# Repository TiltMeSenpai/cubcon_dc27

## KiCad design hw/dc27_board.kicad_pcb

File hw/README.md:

# Defcon 27 Cubcon Badge
Electronic badge from Defcon 27 (2019).  
Contact [@tiltmesenpai](https://twitter.com/TiltMeSenpai) or [@_cubcon](https://twitter.com/_cubcon) on Twitter with any questions.

## Important Eratta
- R1, C17 (On boards given out at Defcon) should be left unpopulated.
  These have been removed in this release.
- Button support components map according to the following table:

| Defcon Board | Post-Defcon Board |
|---|---|
| R2 | R1 |
| R3 | R4 |
| R3 | R2 |
| C16 | C4 |
| C14 | C6 |
| C15 | C5 |

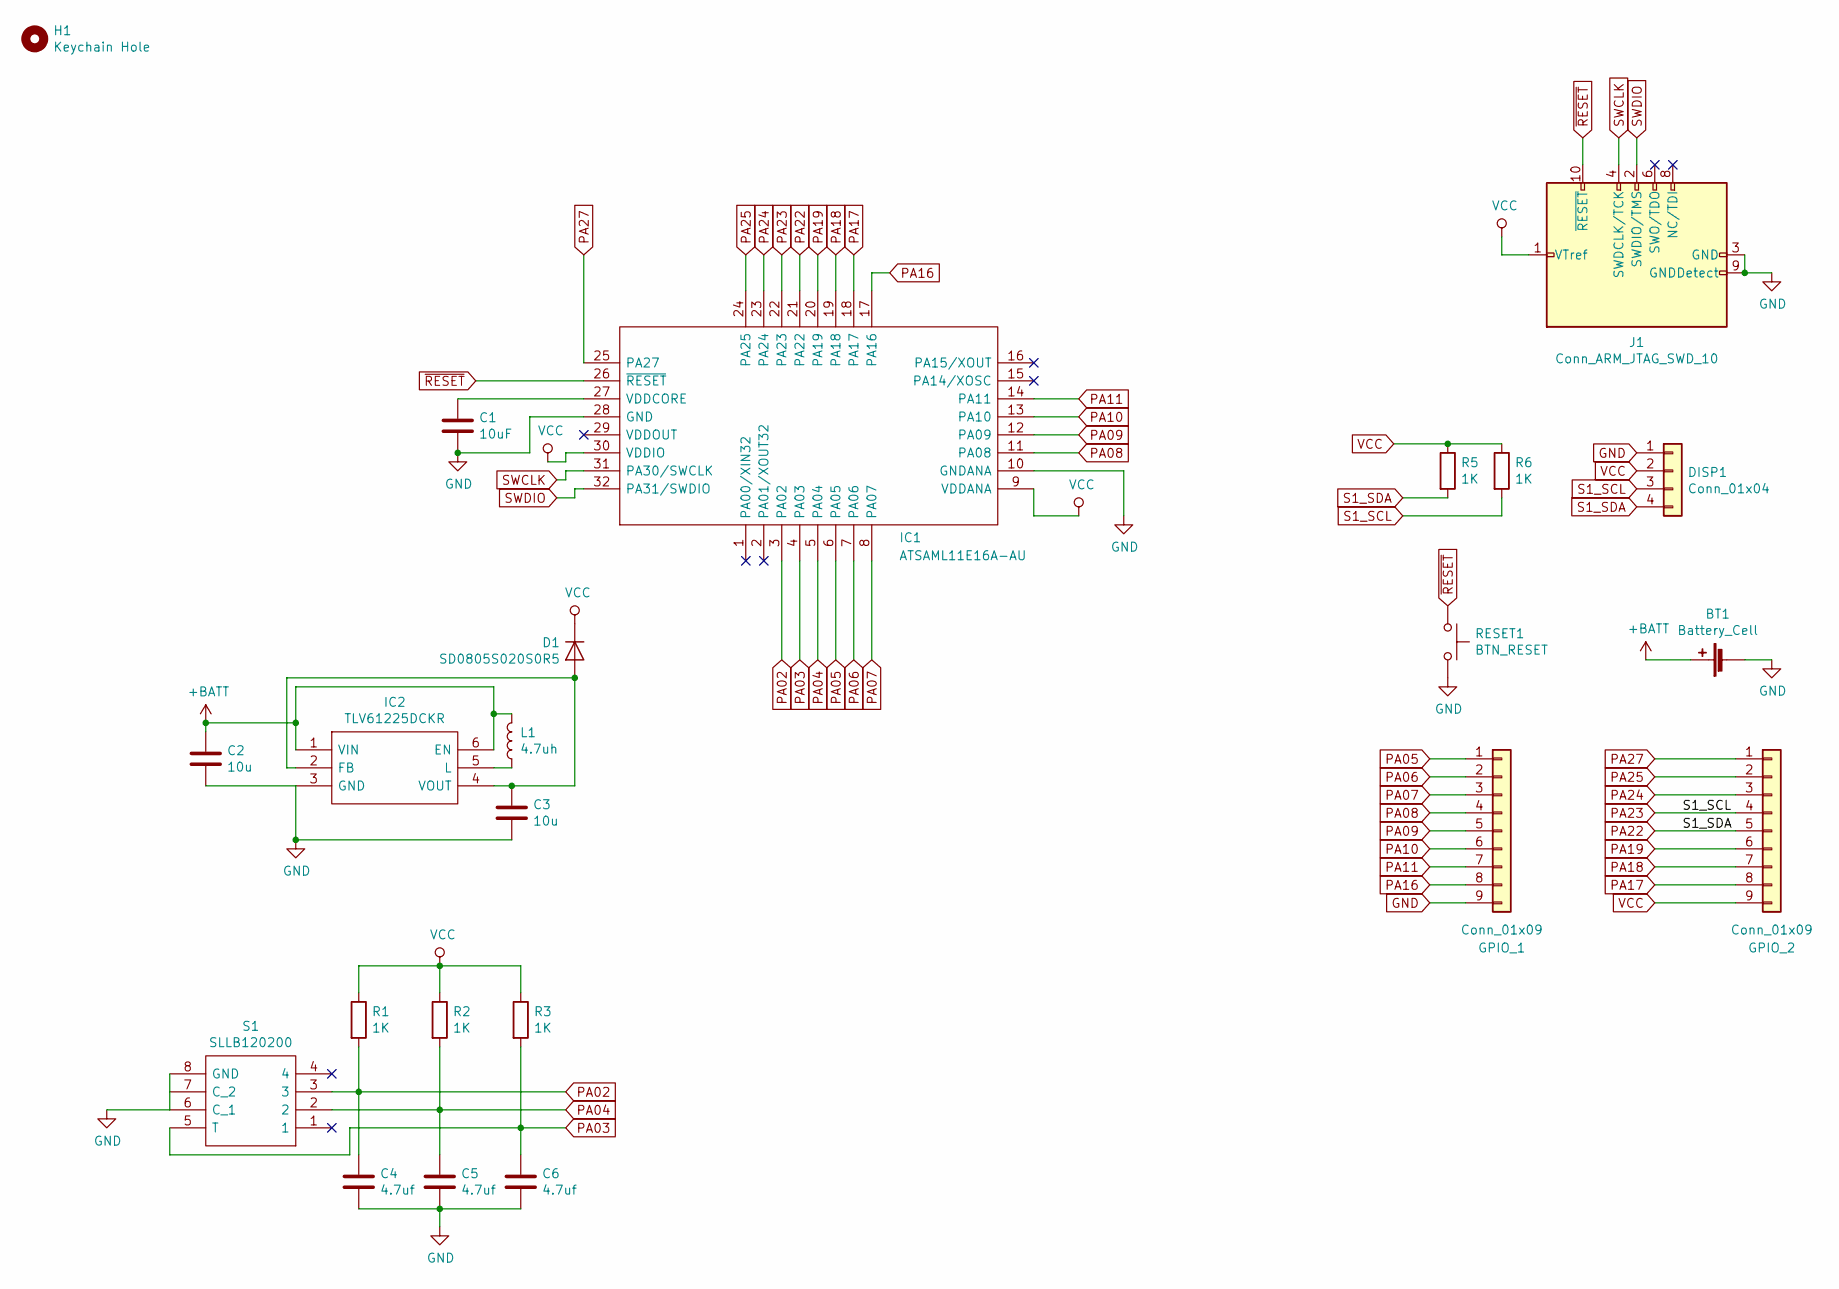
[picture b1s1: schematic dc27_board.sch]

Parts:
BT1: Battery_Cell; 2466; Mouser Part Number 534-2466
C1: 10uF; C_0805_2012Metric_Pad1.15x1.40mm_HandSolder
C2, C3: 10u; C_0805_2012Metric_Pad1.15x1.40mm_HandSolder; Mouser Part Number 80-C0805X106M9RAUTO
C4, C5, C6: 4.7uf; C_0805_2012Metric_Pad1.15x1.40mm_HandSolder
D1: SD0805S020S0R5; D_0805_2012Metric; Mouser Part Number 581-SD0805S020S0R5
DISP1: Conn_01x04; PinHeader_1x04_P2.54mm_Vertical
GPIO_1, GPIO_2: Conn_01x09; PinSocket_1x09_P2.54mm_Vertical
H1: Keychain Hole; MountingHole_2mm
IC1: ATSAML11E16A-AU; QFP80P900X900X120-32N; Mouser Part Number 579-ATSAML11E16A-AU
IC2: TLV61225DCKR; SOT65P210X110-6N; Mouser Part Number 595-TLV61225DCKR
J1: Conn_ARM_JTAG_SWD_10; PinHeader_2x05_P1.27mm_Vertical_SMD; Mouser Part Number 855-M50-3610542
L1: 4.7uh; L_0805_2012Metric_Pad1.15x1.40mm_HandSolder; Mouser Part Number 652-SRN2009T-4R7M
R1, R2, R3: 1K; C_0805_2012Metric_Pad1.15x1.40mm_HandSolder
R5, R6: 1K; R_0805_2012Metric_Pad1.15x1.40mm_HandSolder; Mouser Part Number 667-ERJ-UP6J102V
RESET1: BTN_RESET; SW_SPST_TL3342
S1: SLLB120200; Mouser Part Number 688-SLLB120200

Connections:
+BATT: BT1.1 (+), C2.1, IC2.1 (VIN), IC2.6 (EN), L1.2
GND: BT1.2 (-), C1.2, C2.2, C3.2, C4.2, C5.2, C6.2, DISP1.1, GPIO_1.9, IC1.10 (GNDANA), IC1.28 (GND), IC2.3 (GND), J1.3 (GND), J1.5 (GND), J1.9 (GNDDetect), RESET1.2, S1.6 (C_1), S1.8 (GND)
unnamed: C1.1, IC1.27 (VDDCORE)
unnamed: C3.1, D1.2 (A), IC2.2 (FB), IC2.4 (VOUT)
unnamed: IC2.5 (L), L1.1
PA02: C4.1, IC1.3 (PA02), R1.2, S1.3
PA03: C6.1, IC1.4 (PA03), R3.2, S1.5 (T)
PA04: C5.1, IC1.5 (PA04), R2.2, S1.2
PA05: GPIO_1.1, IC1.6 (PA05)
PA06: GPIO_1.2, IC1.7 (PA06)
PA07: GPIO_1.3, IC1.8 (PA07)
PA08: GPIO_1.4, IC1.11 (PA08)
PA09: GPIO_1.5, IC1.12 (PA09)
PA10: GPIO_1.6, IC1.13 (PA10)
PA11: GPIO_1.7, IC1.14 (PA11)
PA16: GPIO_1.8, IC1.17 (PA16)
PA17: GPIO_2.8, IC1.18 (PA17)
PA18: GPIO_2.7, IC1.19 (PA18)
PA19: GPIO_2.6, IC1.20 (PA19)
PA22: DISP1.4, GPIO_2.5, IC1.21 (PA22), R5.2
PA23: DISP1.3, GPIO_2.4, IC1.22 (PA23), R6.2
PA24: GPIO_2.3, IC1.23 (PA24)
PA25: GPIO_2.2, IC1.24 (PA25)
PA27: GPIO_2.1, IC1.25 (PA27)
SWCLK: IC1.31 (PA30/SWCLK), J1.4 (SWDCLK/TCK)
SWDIO: IC1.32 (PA31/SWDIO), J1.2 (SWDIO/TMS)
VCC: D1.1 (K), DISP1.2, GPIO_2.9, IC1.9 (VDDANA), IC1.30 (VDDIO), J1.1 (VTref), R1.1, R2.1, R3.1, R5.1, R6.1
~RESET: IC1.26 (~RESET), J1.10 (~RESET~), RESET1.1

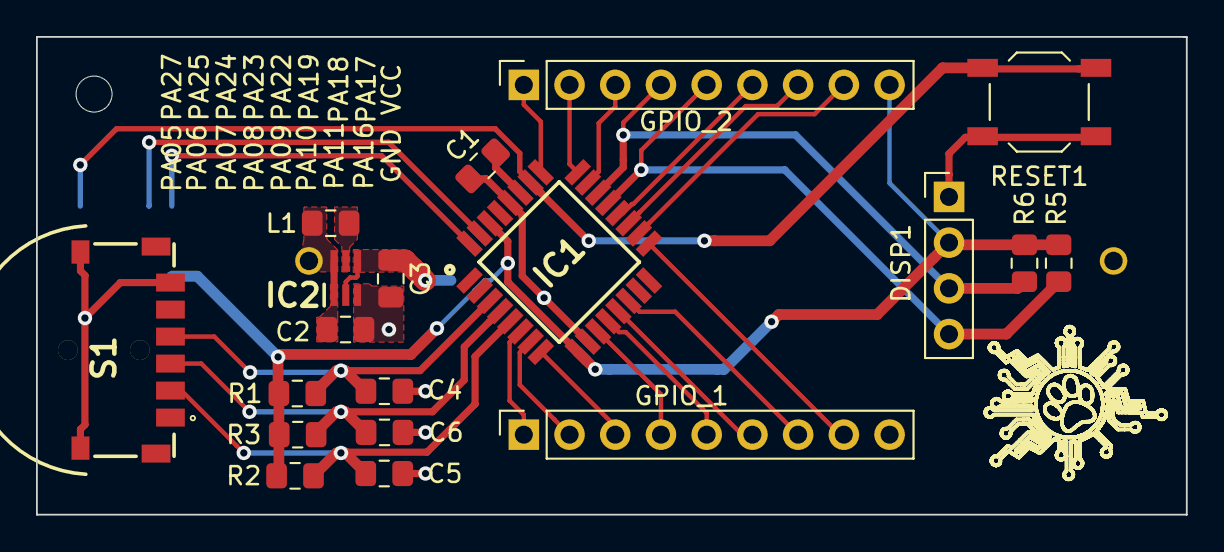
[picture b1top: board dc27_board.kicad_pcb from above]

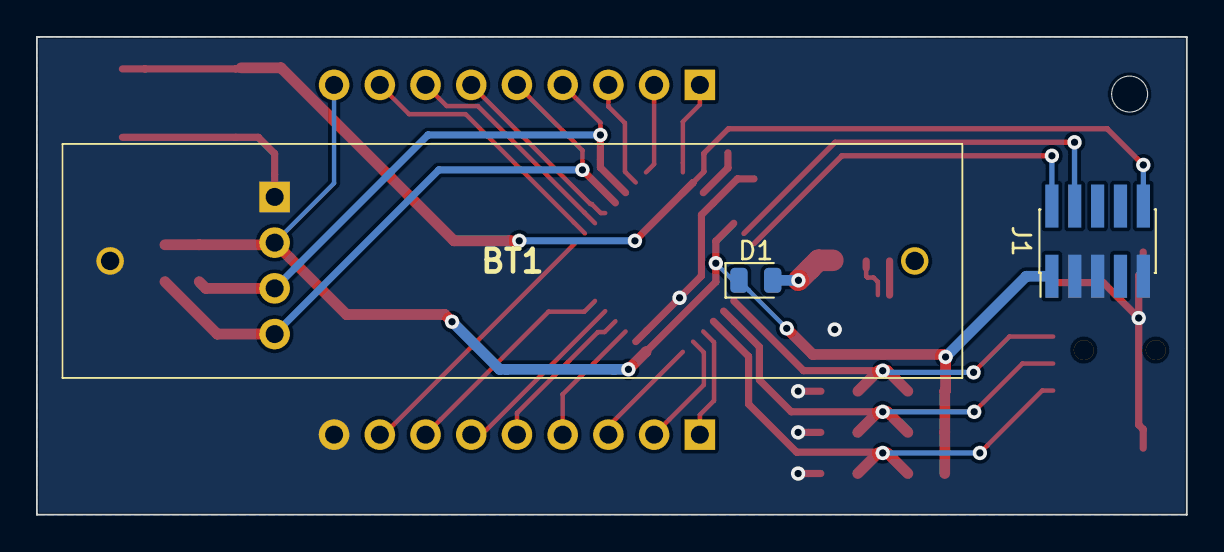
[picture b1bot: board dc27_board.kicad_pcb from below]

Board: 2 copper layers, 63.9 x 26.5 mm, 23 parts (3 on the bottom side), 28 nets.

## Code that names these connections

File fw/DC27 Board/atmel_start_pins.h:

/*
 * Code generated from Atmel Start.
 *
 * This file will be overwritten when reconfiguring your Atmel Start project.
 * Please copy examples or other code you want to keep to a separate file
 * to avoid losing it when reconfiguring.
 */
#ifndef ATMEL_START_PINS_H_INCLUDED
#define ATMEL_START_PINS_H_INCLUDED

#include <hal_gpio.h>

// SAML11 has 9 pin functions

#define GPIO_PIN_FUNCTION_A 0
#define GPIO_PIN_FUNCTION_B 1
#define GPIO_PIN_FUNCTION_C 2
#define GPIO_PIN_FUNCTION_D 3
#define GPIO_PIN_FUNCTION_E 4
#define GPIO_PIN_FUNCTION_F 5
#define GPIO_PIN_FUNCTION_G 6
#define GPIO_PIN_FUNCTION_H 7
#define GPIO_PIN_FUNCTION_I 8

#define PA02 GPIO(GPIO_PORTA, 2)
#define PA03 GPIO(GPIO_PORTA, 3)
#define PA04 GPIO(GPIO_PORTA, 4)
#define PA05 GPIO(GPIO_PORTA, 5)
#define PA06 GPIO(GPIO_PORTA, 6)
#define PA07 GPIO(GPIO_PORTA, 7)
#define PA08 GPIO(GPIO_PORTA, 8)
#define PA09 GPIO(GPIO_PORTA, 9)
#define PA10 GPIO(GPIO_PORTA, 10)
#define PA11 GPIO(GPIO_PORTA, 11)
#define PA16 GPIO(GPIO_PORTA, 16)
#define PA17 GPIO(GPIO_PORTA, 17)
#define PA18 GPIO(GPIO_PORTA, 18)
#define PA19 GPIO(GPIO_PORTA, 19)
#define PA22 GPIO(GPIO_PORTA, 22)
#define PA23 GPIO(GPIO_PORTA, 23)
#define PA24 GPIO(GPIO_PORTA, 24)
#define PA25 GPIO(GPIO_PORTA, 25)
#define PA27 GPIO(GPIO_PORTA, 27)

#endif // ATMEL_START_PINS_H_INCLUDED

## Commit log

2019-08-14 Release hw
2019-08-14 Init fw
2019-08-14 added bom files
